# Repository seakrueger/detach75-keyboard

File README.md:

# detach75-keyboard
A 75% mechanical keyboard created for my high school PLTW capstone course. On top of being a standard mechanical keyboard, there is an integrated USB 2.0 hub with a second USB data line exposed internally. This allowed a 2.4 GHz USB receiver to be soldered on and connect to a wireless number pad for expanded functionality. 

## PCB
The design and layout of the PCB would not have been possible without this [series of articles](https://www.masterzen.fr/tag/#pcb) from Masterzen. Following his process, I adapted the matrix from a 60% layout to a 75% layout and integrated the USB 2.0 hub IC onto the USB D+/- lines. The PCB is relatively basic, being only two layers and missing several elements such as ground pours. The manufactured version of the PCB had two incorrectly placed capacitors that prevented the MCU from staying on and had to be removed; the included CAD files have been corrected. 

## Firmware
The keyboard uses the widely popular QMK firmware. QMK is the firmware of choice among keyboard enthusiasts as it is easily customizable with a rich set of features. Included is the configuration for the PCB's switch matrix as well as a basic setup of modifier keys.

To flash the PCB's MCU, first set up QMK following their guide [here](https://docs.qmk.fm/newbs_getting_started). Then, copy the contents of the Firmware directory into the QMK keyboard directory. Compile the firmware with `qmk compile -kb detach/75 -km default` and flash using QMK's [flashing guide](https://docs.qmk.fm/newbs_flashing). Use the reset push button on the underside of the PCB to initiate the ATmega bootloader; the MCU can be flashed via the USB-C port.

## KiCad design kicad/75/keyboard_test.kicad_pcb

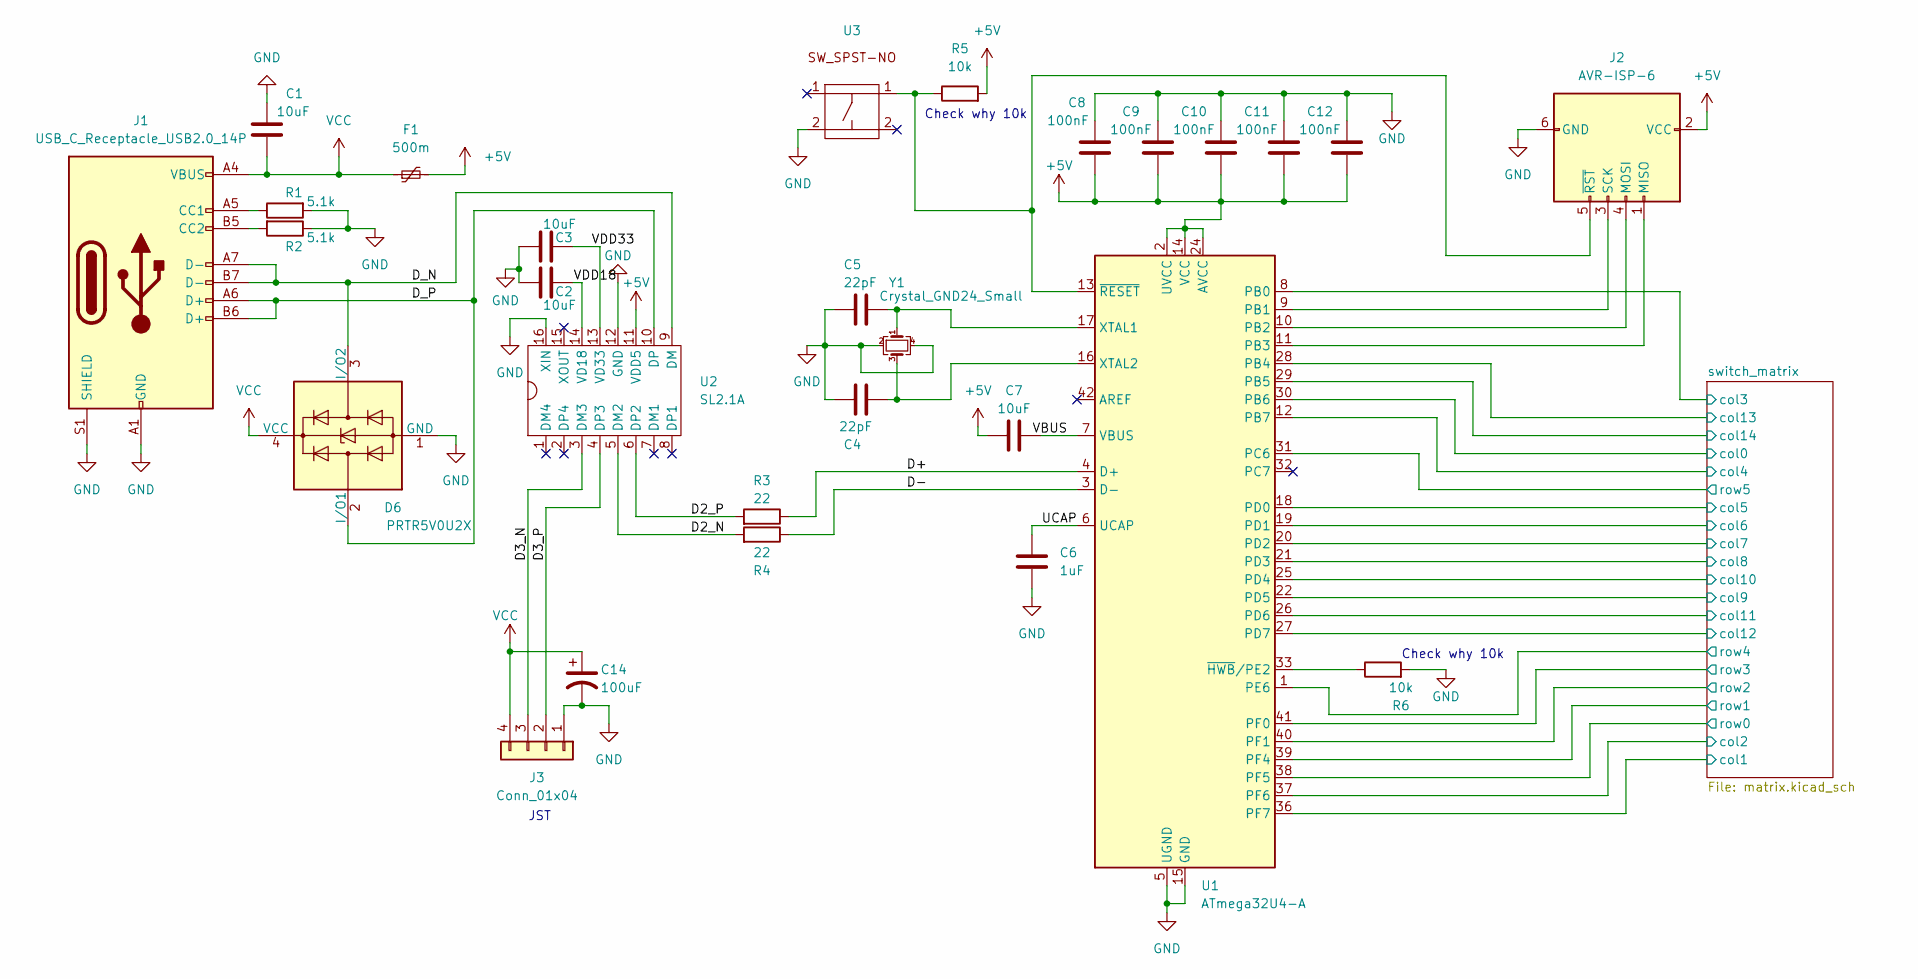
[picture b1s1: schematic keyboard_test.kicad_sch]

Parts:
C1, C2, C3, C7: 10uF; C_0805_2012Metric_Pad1.18x1.45mm_HandSolder; LCSC C95841
C4, C5: 22pF; C_0805_2012Metric_Pad1.18x1.45mm_HandSolder; LCSC C1804
C6: 1uF; C_0805_2012Metric_Pad1.18x1.45mm_HandSolder; LCSC C116352
C8, C9, C10, C11, C12: 100nF; C_0805_2012Metric_Pad1.18x1.45mm_HandSolder; LCSC C346219
C14: 100uF; C_Elec_6.3x5.4; LCSC C111600
D6: PRTR5V0U2X; SOT-143; LCSC C2827688
F1: 500m; Fuse_1206_3216Metric_Pad1.42x1.75mm_HandSolder; LCSC C70069
J1: USB_C_Receptacle_USB2.0_14P; USB_C_Receptacle_HRO_TYPE-C-31-M-12; LCSC C165948
J2: AVR-ISP-6; Reset_Pretty-Mask
J3: Conn_01x04; JST_SH_SM04B-SRSS-TB_1x04-1MP_P1.00mm_Horizontal
R1, R2: 5.1k; R_0805_2012Metric_Pad1.20x1.40mm_HandSolder; LCSC C27834
R3, R4: 22; R_0805_2012Metric_Pad1.20x1.40mm_HandSolder; LCSC C17561
R5, R6: 10k; R_0805_2012Metric_Pad1.20x1.40mm_HandSolder; LCSC C17402
U1: ATmega32U4-A; TQFP-44_10x10mm_P0.8mm; LCSC C44854
U2: SL2.1A; SO16; LCSC C6798314
U3: SW_SPST_SKQG_WithStem; LCSC C115351
Y1: Crystal_GND24_Small; Crystal_SMD_3225-4Pin_3.2x2.5mm_HandSoldering; LCSC C255909

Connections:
+5V: C7.1, C8.1, C9.1, C10.1, C11.1, C12.1, F1.2, J2.2 (VCC), R5.2, U1.2 (UVCC), U1.14 (VCC), U1.24 (AVCC), U1.34 (VCC), U1.44 (AVCC), U2.11 (VDD5)
/D2_N: R4.2, U2.5 (DM2)
/D2_P: R3.2, U2.6 (DP2)
/D3_N: J3.3, U2.3 (DM3)
/D3_P: J3.2, U2.4 (DP3)
/D+: R3.1, U1.4 (D+)
/D-: R4.1, U1.3 (D-)
/D_N: D6.3 (I/O2), J1.A7 (D-), J1.B7 (D-), U2.9 (DM)
/D_P: D6.2 (I/O1), J1.A6 (D+), J1.B6 (D+), U2.10 (DP)
/UCAP: C6.1, U1.6 (UCAP)
/VBUS: C7.2, U1.7 (VBUS)
/VDD18: C2.1, U2.14 (VD18)
/VDD33: C3.1, U2.13 (VD33)
/switch_matrix/col0: U1.30 (PB6); also elsewhere on the board
/switch_matrix/col1: U1.36 (PF7); also elsewhere on the board
/switch_matrix/col2: U1.37 (PF6); also elsewhere on the board
/switch_matrix/col3: U1.8 (PB0); also elsewhere on the board
/switch_matrix/col4: U1.12 (PB7); also elsewhere on the board
/switch_matrix/col5: U1.18 (PD0); also elsewhere on the board
/switch_matrix/col6: U1.19 (PD1); also elsewhere on the board
/switch_matrix/col7: U1.20 (PD2); also elsewhere on the board
/switch_matrix/col8: U1.21 (PD3); also elsewhere on the board
/switch_matrix/col9: U1.22 (PD5); also elsewhere on the board
/switch_matrix/col10: U1.25 (PD4); also elsewhere on the board
/switch_matrix/col11: U1.26 (PD6); also elsewhere on the board
/switch_matrix/col12: U1.27 (PD7); also elsewhere on the board
/switch_matrix/col13: U1.28 (PB4); also elsewhere on the board
/switch_matrix/col14: U1.29 (PB5); also elsewhere on the board
/switch_matrix/row0: U1.38 (PF5); also elsewhere on the board
/switch_matrix/row1: U1.39 (PF4); also elsewhere on the board
/switch_matrix/row2: U1.40 (PF1); also elsewhere on the board
/switch_matrix/row3: U1.41 (PF0); also elsewhere on the board
/switch_matrix/row4: U1.1 (PE6); also elsewhere on the board
/switch_matrix/row5: U1.31 (PC6); also elsewhere on the board
GND: C1.1, C2.2, C3.2, C4.2, C5.2, C6.2, C8.2, C9.2, C10.2, C11.2, C12.2, C14.2, D6.1 (GND), J1.A1 (GND), J1.A12 (GND), J1.B1 (GND), J1.B12 (GND), J1.S1 (SHIELD), J2.6 (GND), J3.1, R1.2, R2.1, R6.2, U1.5 (UGND), U1.15 (GND), U1.23 (GND), U1.35 (GND), U1.43 (GND), U2.12 (GND), U2.16 (XIN), U3.2, Y1.2, Y1.4
unnamed: J1.A5 (CC1), R1.1
unnamed: J1.B5 (CC2), R2.2
unnamed: J2.1 (MISO), U1.11 (PB3)
unnamed: J2.4 (MOSI), U1.10 (PB2)
unnamed: J2.3 (SCK), U1.9 (PB1)
unnamed: J2.5 (~RST), R5.1, U1.13 (~RESET), U3.1
unnamed: C5.1, U1.17 (XTAL1), Y1.1
unnamed: C4.1, U1.16 (XTAL2), Y1.3
unnamed: R6.1, U1.33 (~HWB/PE2)
VCC: C1.2, C14.1, D6.4 (VCC), F1.1, J1.A4 (VBUS), J1.A9 (VBUS), J1.B4 (VBUS), J1.B9 (VBUS), J3.4

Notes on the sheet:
Check why 10k
JST

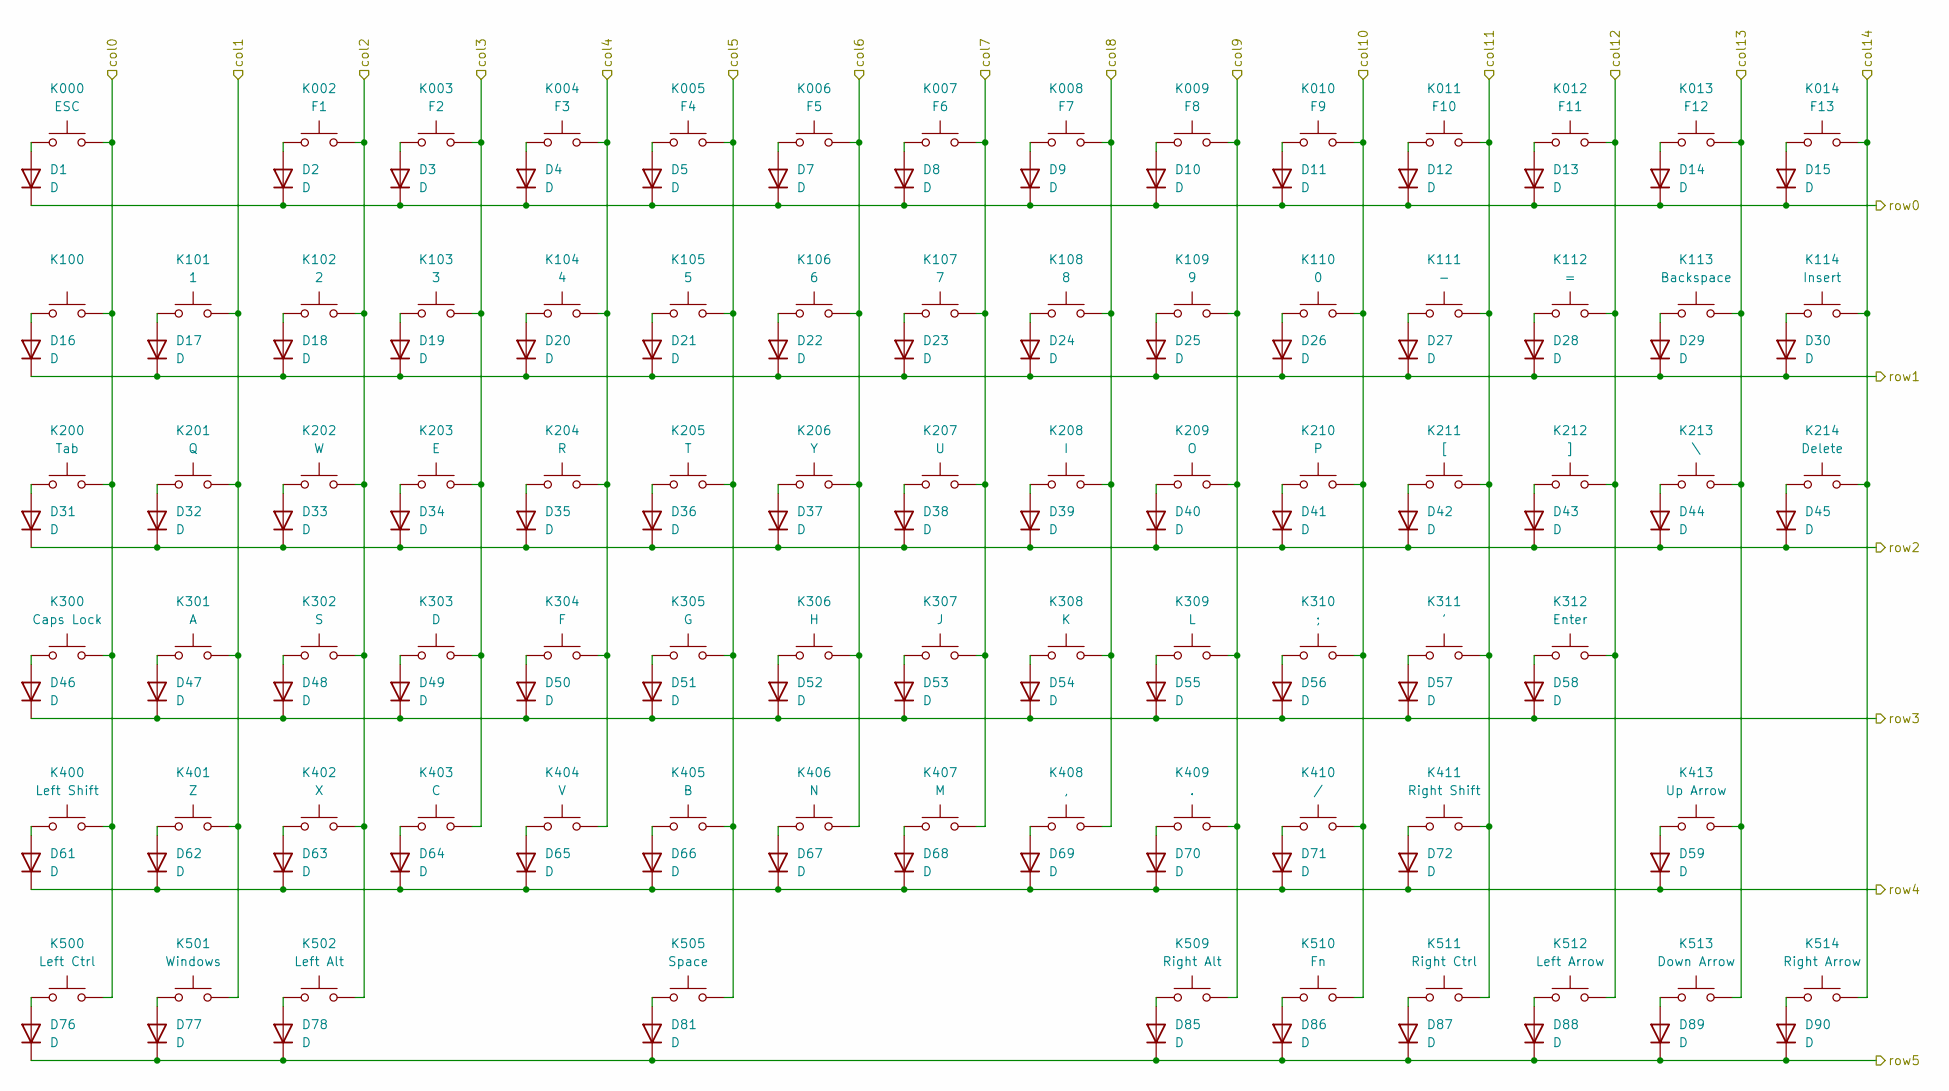
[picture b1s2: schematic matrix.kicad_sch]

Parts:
D1, D2, D3, D4, D5, D7, D8, D9, D10, D11, D12, D13, D14, D15, D16, D17, D18, D19, D20, D21, D22, D23, D24, D25, D26, D27, D28, D29, D30, D31, D32, D33, D34, D35, D36, D37, D38, D39, D40, D41, D42, D43, D44, D45, D46, D47, D48, D49, D50, D51, D52, D53, D54, D55, D56, D57, D58, D59, D61, D62, D63, D64, D65, D66, D67, D68, D69, D70, D71, D72, D76, D77, D78, D81, D85, D86, D87, D88, D89, D90: D; D_SOD-123; LCSC C77978
K000: ESC; SW_Hotswap_Kailh_MX_1.00u
K002: F1; SW_Hotswap_Kailh_MX_1.00u
K003: F2; SW_Hotswap_Kailh_MX_1.00u
K004: F3; SW_Hotswap_Kailh_MX_1.00u
K005: F4; SW_Hotswap_Kailh_MX_1.00u
K006: F5; SW_Hotswap_Kailh_MX_1.00u
K007: F6; SW_Hotswap_Kailh_MX_1.00u
K008: F7; SW_Hotswap_Kailh_MX_1.00u
K009: F8; SW_Hotswap_Kailh_MX_1.00u
K010: F9; SW_Hotswap_Kailh_MX_1.00u
K011: F10; SW_Hotswap_Kailh_MX_1.00u
K012: F11; SW_Hotswap_Kailh_MX_1.00u
K013: F12; SW_Hotswap_Kailh_MX_1.00u
K014: F13; SW_Hotswap_Kailh_MX_1.00u
K100: SW_Hotswap_Kailh_MX_1.00u
K101: 1; SW_Hotswap_Kailh_MX_1.00u
K102: 2; SW_Hotswap_Kailh_MX_1.00u
K103: 3; SW_Hotswap_Kailh_MX_1.00u
K104: 4; SW_Hotswap_Kailh_MX_1.00u
K105: 5; SW_Hotswap_Kailh_MX_1.00u
K106: 6; SW_Hotswap_Kailh_MX_1.00u
K107: 7; SW_Hotswap_Kailh_MX_1.00u
K108: 8; SW_Hotswap_Kailh_MX_1.00u
K109: 9; SW_Hotswap_Kailh_MX_1.00u
K110: 0; SW_Hotswap_Kailh_MX_1.00u
K111: -; SW_Hotswap_Kailh_MX_1.00u
K112: =; SW_Hotswap_Kailh_MX_1.00u
K113: Backspace; SW_Hotswap_Kailh_MX_2.00u
K114: Insert; SW_Hotswap_Kailh_MX_1.00u
K200: Tab; SW_Hotswap_Kailh_MX_1.50u
K201: Q; SW_Hotswap_Kailh_MX_1.00u
K202: W; SW_Hotswap_Kailh_MX_1.00u
K203: E; SW_Hotswap_Kailh_MX_1.00u
K204: R; SW_Hotswap_Kailh_MX_1.00u
K205: T; SW_Hotswap_Kailh_MX_1.00u
K206: Y; SW_Hotswap_Kailh_MX_1.00u
K207: U; SW_Hotswap_Kailh_MX_1.00u
K208: I; SW_Hotswap_Kailh_MX_1.00u
K209: O; SW_Hotswap_Kailh_MX_1.00u
K210: P; SW_Hotswap_Kailh_MX_1.00u
K211: [; SW_Hotswap_Kailh_MX_1.00u
K212: ]; SW_Hotswap_Kailh_MX_1.00u
K213: \; SW_Hotswap_Kailh_MX_1.50u
K214: Delete; SW_Hotswap_Kailh_MX_1.00u
K300: Caps Lock; SW_Hotswap_Kailh_MX_1.75u
K301: A; SW_Hotswap_Kailh_MX_1.00u
K302: S; SW_Hotswap_Kailh_MX_1.00u
K303: D; SW_Hotswap_Kailh_MX_1.00u
K304: F; SW_Hotswap_Kailh_MX_1.00u
K305: G; SW_Hotswap_Kailh_MX_1.00u
K306: H; SW_Hotswap_Kailh_MX_1.00u
K307: J; SW_Hotswap_Kailh_MX_1.00u
K308: K; SW_Hotswap_Kailh_MX_1.00u
K309: L; SW_Hotswap_Kailh_MX_1.00u
K310: ;; SW_Hotswap_Kailh_MX_1.00u
K311: '; SW_Hotswap_Kailh_MX_1.00u
K312: Enter; SW_Hotswap_Kailh_MX_2.25u
K400: Left Shift; SW_Hotswap_Kailh_MX_2.25u
K401: Z; SW_Hotswap_Kailh_MX_1.00u
K402: X; SW_Hotswap_Kailh_MX_1.00u
K403: C; SW_Hotswap_Kailh_MX_1.00u
K404: V; SW_Hotswap_Kailh_MX_1.00u
K405: B; SW_Hotswap_Kailh_MX_1.00u
K406: N; SW_Hotswap_Kailh_MX_1.00u
K407: M; SW_Hotswap_Kailh_MX_1.00u
K408: ,; SW_Hotswap_Kailh_MX_1.00u
K409: .; SW_Hotswap_Kailh_MX_1.00u
K410: /; SW_Hotswap_Kailh_MX_1.00u
K411: Right Shift; SW_Hotswap_Kailh_MX_1.75u
K413: Up Arrow; SW_Hotswap_Kailh_MX_1.00u
K500: Left Ctrl; SW_Hotswap_Kailh_MX_1.25u
K501: Windows; SW_Hotswap_Kailh_MX_1.25u
K502: Left Alt; SW_Hotswap_Kailh_MX_1.25u
K505: Space; SW_Hotswap_Kailh_MX_6.25u
K509: Right Alt; SW_Hotswap_Kailh_MX_1.00u
K510: Fn; SW_Hotswap_Kailh_MX_1.00u
K511: Right Ctrl; SW_Hotswap_Kailh_MX_1.00u
K512: Left Arrow; SW_Hotswap_Kailh_MX_1.00u
K513: Down Arrow; SW_Hotswap_Kailh_MX_1.00u
K514: Right Arrow; SW_Hotswap_Kailh_MX_1.00u

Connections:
/switch_matrix/col0: K000.2, K100.2, K200.2, K300.2, K400.2, K500.2; also elsewhere on the board
/switch_matrix/col1: K101.2, K201.2, K301.2, K401.2, K501.2; also elsewhere on the board
/switch_matrix/col2: K002.2, K102.2, K202.2, K302.2, K402.2, K502.2; also elsewhere on the board
/switch_matrix/col3: K003.2, K103.2, K203.2, K303.2, K403.2; also elsewhere on the board
/switch_matrix/col4: K004.2, K104.2, K204.2, K304.2, K404.2; also elsewhere on the board
/switch_matrix/col5: K005.2, K105.2, K205.2, K305.2, K405.2, K505.2; also elsewhere on the board
/switch_matrix/col6: K006.2, K106.2, K206.2, K306.2, K406.2; also elsewhere on the board
/switch_matrix/col7: K007.2, K107.2, K207.2, K307.2, K407.2; also elsewhere on the board
/switch_matrix/col8: K008.2, K108.2, K208.2, K308.2, K408.2; also elsewhere on the board
/switch_matrix/col9: K009.2, K109.2, K209.2, K309.2, K409.2, K509.2; also elsewhere on the board
/switch_matrix/col10: K010.2, K110.2, K210.2, K310.2, K410.2, K510.2; also elsewhere on the board
/switch_matrix/col11: K011.2, K111.2, K211.2, K311.2, K411.2, K511.2; also elsewhere on the board
/switch_matrix/col12: K012.2, K112.2, K212.2, K312.2, K512.2; also elsewhere on the board
/switch_matrix/col13: K013.2, K113.2, K213.2, K413.2, K513.2; also elsewhere on the board
/switch_matrix/col14: K014.2, K114.2, K214.2, K514.2; also elsewhere on the board
/switch_matrix/row0: D1.1 (K), D2.1 (K), D3.1 (K), D4.1 (K), D5.1 (K), D7.1 (K), D8.1 (K), D9.1 (K), D10.1 (K), D11.1 (K), D12.1 (K), D13.1 (K), D14.1 (K), D15.1 (K); also elsewhere on the board
/switch_matrix/row1: D16.1 (K), D17.1 (K), D18.1 (K), D19.1 (K), D20.1 (K), D21.1 (K), D22.1 (K), D23.1 (K), D24.1 (K), D25.1 (K), D26.1 (K), D27.1 (K), D28.1 (K), D29.1 (K), D30.1 (K); also elsewhere on the board
/switch_matrix/row2: D31.1 (K), D32.1 (K), D33.1 (K), D34.1 (K), D35.1 (K), D36.1 (K), D37.1 (K), D38.1 (K), D39.1 (K), D40.1 (K), D41.1 (K), D42.1 (K), D43.1 (K), D44.1 (K), D45.1 (K); also elsewhere on the board
/switch_matrix/row3: D46.1 (K), D47.1 (K), D48.1 (K), D49.1 (K), D50.1 (K), D51.1 (K), D52.1 (K), D53.1 (K), D54.1 (K), D55.1 (K), D56.1 (K), D57.1 (K), D58.1 (K); also elsewhere on the board
/switch_matrix/row4: D59.1 (K), D61.1 (K), D62.1 (K), D63.1 (K), D64.1 (K), D65.1 (K), D66.1 (K), D67.1 (K), D68.1 (K), D69.1 (K), D70.1 (K), D71.1 (K), D72.1 (K); also elsewhere on the board
/switch_matrix/row5: D76.1 (K), D77.1 (K), D78.1 (K), D81.1 (K), D85.1 (K), D86.1 (K), D87.1 (K), D88.1 (K), D89.1 (K), D90.1 (K); also elsewhere on the board
unnamed: D1.2 (A), K000.1
unnamed: D2.2 (A), K002.1
unnamed: D3.2 (A), K003.1
unnamed: D4.2 (A), K004.1
unnamed: D5.2 (A), K005.1
unnamed: D7.2 (A), K006.1
unnamed: D8.2 (A), K007.1
unnamed: D9.2 (A), K008.1
unnamed: D10.2 (A), K009.1
unnamed: D11.2 (A), K010.1
unnamed: D12.2 (A), K011.1
unnamed: D13.2 (A), K012.1
unnamed: D14.2 (A), K013.1
unnamed: D15.2 (A), K014.1
unnamed: D16.2 (A), K100.1
unnamed: D17.2 (A), K101.1
unnamed: D18.2 (A), K102.1
unnamed: D19.2 (A), K103.1
unnamed: D20.2 (A), K104.1
unnamed: D21.2 (A), K105.1
unnamed: D22.2 (A), K106.1
unnamed: D23.2 (A), K107.1
unnamed: D24.2 (A), K108.1
unnamed: D25.2 (A), K109.1
unnamed: D26.2 (A), K110.1
unnamed: D27.2 (A), K111.1
unnamed: D28.2 (A), K112.1
unnamed: D29.2 (A), K113.1
unnamed: D30.2 (A), K114.1
unnamed: D31.2 (A), K200.1
unnamed: D32.2 (A), K201.1
unnamed: D33.2 (A), K202.1
unnamed: D34.2 (A), K203.1
unnamed: D35.2 (A), K204.1
unnamed: D36.2 (A), K205.1
unnamed: D37.2 (A), K206.1
unnamed: D38.2 (A), K207.1
unnamed: D39.2 (A), K208.1
unnamed: D40.2 (A), K209.1
unnamed: D41.2 (A), K210.1
unnamed: D42.2 (A), K211.1
unnamed: D43.2 (A), K212.1
unnamed: D44.2 (A), K213.1
unnamed: D45.2 (A), K214.1
unnamed: D46.2 (A), K300.1
unnamed: D47.2 (A), K301.1
unnamed: D48.2 (A), K302.1
unnamed: D49.2 (A), K303.1
unnamed: D50.2 (A), K304.1
unnamed: D51.2 (A), K305.1
unnamed: D52.2 (A), K306.1
unnamed: D53.2 (A), K307.1
unnamed: D54.2 (A), K308.1
unnamed: D55.2 (A), K309.1
unnamed: D56.2 (A), K310.1
unnamed: D57.2 (A), K311.1
unnamed: D58.2 (A), K312.1
unnamed: D59.2 (A), K413.1
unnamed: D61.2 (A), K400.1
unnamed: D62.2 (A), K401.1
unnamed: D63.2 (A), K402.1
unnamed: D64.2 (A), K403.1
unnamed: D65.2 (A), K404.1
unnamed: D66.2 (A), K405.1
unnamed: D67.2 (A), K406.1
unnamed: D68.2 (A), K407.1
unnamed: D69.2 (A), K408.1
unnamed: D70.2 (A), K409.1
unnamed: D71.2 (A), K410.1
unnamed: D72.2 (A), K411.1
unnamed: D76.2 (A), K500.1
unnamed: D77.2 (A), K501.1
unnamed: D78.2 (A), K502.1
unnamed: D81.2 (A), K505.1
unnamed: D85.2 (A), K509.1
unnamed: D86.2 (A), K510.1
unnamed: D87.2 (A), K511.1
unnamed: D88.2 (A), K512.1
unnamed: D89.2 (A), K513.1
unnamed: D90.2 (A), K514.1

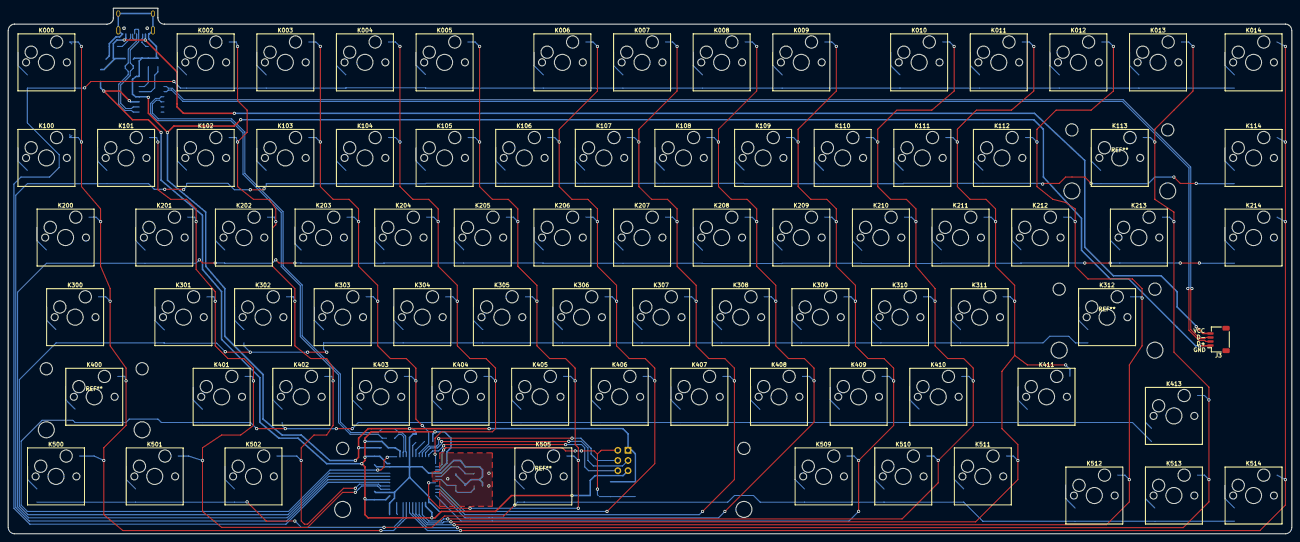
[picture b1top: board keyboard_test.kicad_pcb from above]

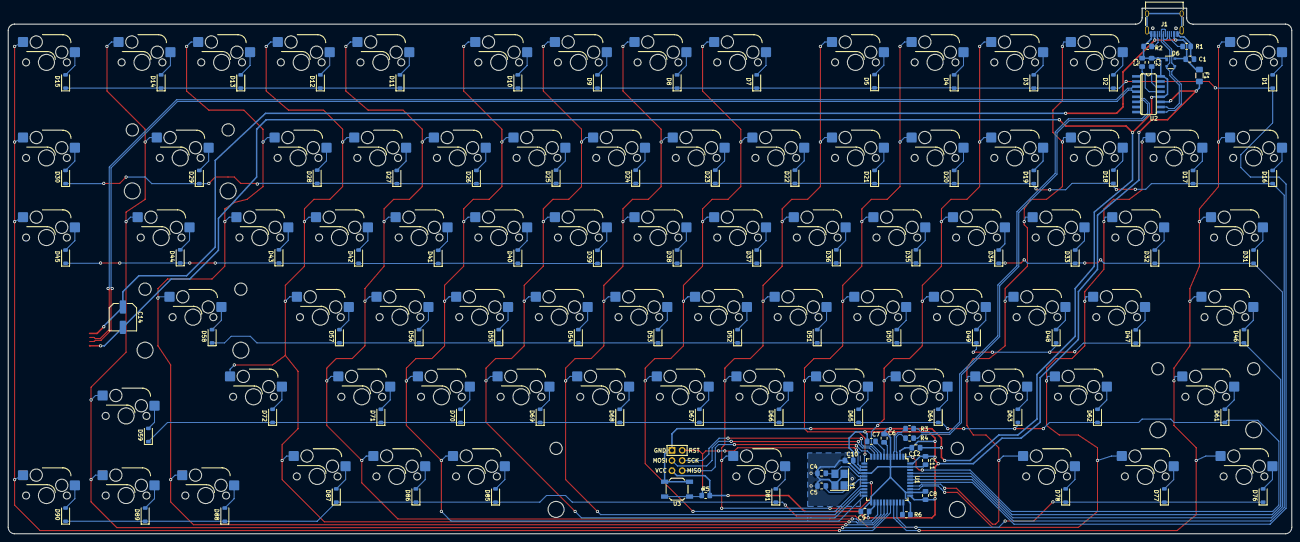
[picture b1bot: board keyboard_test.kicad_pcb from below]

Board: 2 copper layers, 319.9 x 131.0 mm, 188 parts (107 on the bottom side), 125 nets.

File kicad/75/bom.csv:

Comment,Designator,Footprint,LCSC
10uF,"C1,C2,C3,C7",C_0805_2012Metric_Pad1.18x1.45mm_HandSolder,C95841
100uF,C14,C_Elec_6.3x5.4,C111600
22pF,"C4,C5",C_0805_2012Metric_Pad1.18x1.45mm_HandSolder,C1804
1uF,C6,C_0805_2012Metric_Pad1.18x1.45mm_HandSolder,C116352
100nF,"C8,C9,C10,C11,C12",C_0805_2012Metric_Pad1.18x1.45mm_HandSolder,C346219
D,"D1,D2,D3,D4,D5,D7,D8,D9,D10,D11,D12,D13,D14,D15,D16,D17,D18,D19,D20,D21,D22,D23,D24,D25,D26,D27,D28,D29,D30,D31,D32,D33,D34,D35,D36,D37,D38,D39,D40,D41,D42,D43,D44,D45,D46,D47,D48,D49,D50,D51,D52,D53,D54,D55,D56,D57,D58,D59,D61,D62,D63,D64,D65,D66,D67,D68,D69,D70,D71,D72,D76,D77,D78,D81,D85,D86,D87,D88,D89,D90",D_SOD-123,C77978
PRTR5V0U2X,D6,SOT-143,C2827688
500m,F1,Fuse_1206_3216Metric_Pad1.42x1.75mm_HandSolder,C70069
USB_C_Receptacle_USB2.0_14P,J1,USB_C_Receptacle_HRO_TYPE-C-31-M-12,C165948
AVR-ISP-6,J2,random-keyboard-parts:Reset_Pretty-Mask,
Conn_01x04,J3,Connector_JST:JST_SH_SM04B-SRSS-TB_1x04-1MP_P1.00mm_Horizontal,
ESC,K000,PCM_Switch_Keyboard_Hotswap_Kailh:SW_Hotswap_Kailh_MX_1.00u,
F1,K002,PCM_Switch_Keyboard_Hotswap_Kailh:SW_Hotswap_Kailh_MX_1.00u,
F2,K003,PCM_Switch_Keyboard_Hotswap_Kailh:SW_Hotswap_Kailh_MX_1.00u,
F3,K004,PCM_Switch_Keyboard_Hotswap_Kailh:SW_Hotswap_Kailh_MX_1.00u,
F4,K005,PCM_Switch_Keyboard_Hotswap_Kailh:SW_Hotswap_Kailh_MX_1.00u,
F5,K006,PCM_Switch_Keyboard_Hotswap_Kailh:SW_Hotswap_Kailh_MX_1.00u,
F6,K007,PCM_Switch_Keyboard_Hotswap_Kailh:SW_Hotswap_Kailh_MX_1.00u,
F7,K008,PCM_Switch_Keyboard_Hotswap_Kailh:SW_Hotswap_Kailh_MX_1.00u,
F8,K009,PCM_Switch_Keyboard_Hotswap_Kailh:SW_Hotswap_Kailh_MX_1.00u,
F9,K010,PCM_Switch_Keyboard_Hotswap_Kailh:SW_Hotswap_Kailh_MX_1.00u,
F10,K011,PCM_Switch_Keyboard_Hotswap_Kailh:SW_Hotswap_Kailh_MX_1.00u,
F11,K012,PCM_Switch_Keyboard_Hotswap_Kailh:SW_Hotswap_Kailh_MX_1.00u,
F12,K013,PCM_Switch_Keyboard_Hotswap_Kailh:SW_Hotswap_Kailh_MX_1.00u,
F13,K014,PCM_Switch_Keyboard_Hotswap_Kailh:SW_Hotswap_Kailh_MX_1.00u,
~,K100,PCM_Switch_Keyboard_Hotswap_Kailh:SW_Hotswap_Kailh_MX_1.00u,
1,K101,PCM_Switch_Keyboard_Hotswap_Kailh:SW_Hotswap_Kailh_MX_1.00u,
2,K102,PCM_Switch_Keyboard_Hotswap_Kailh:SW_Hotswap_Kailh_MX_1.00u,
3,K103,PCM_Switch_Keyboard_Hotswap_Kailh:SW_Hotswap_Kailh_MX_1.00u,
4,K104,PCM_Switch_Keyboard_Hotswap_Kailh:SW_Hotswap_Kailh_MX_1.00u,
5,K105,PCM_Switch_Keyboard_Hotswap_Kailh:SW_Hotswap_Kailh_MX_1.00u,
6,K106,PCM_Switch_Keyboard_Hotswap_Kailh:SW_Hotswap_Kailh_MX_1.00u,
7,K107,PCM_Switch_Keyboard_Hotswap_Kailh:SW_Hotswap_Kailh_MX_1.00u,
8,K108,PCM_Switch_Keyboard_Hotswap_Kailh:SW_Hotswap_Kailh_MX_1.00u,
9,K109,PCM_Switch_Keyboard_Hotswap_Kailh:SW_Hotswap_Kailh_MX_1.00u,
0,K110,PCM_Switch_Keyboard_Hotswap_Kailh:SW_Hotswap_Kailh_MX_1.00u,
-,K111,PCM_Switch_Keyboard_Hotswap_Kailh:SW_Hotswap_Kailh_MX_1.00u,
=,K112,PCM_Switch_Keyboard_Hotswap_Kailh:SW_Hotswap_Kailh_MX_1.00u,
Backspace,K113,PCM_Switch_Keyboard_Hotswap_Kailh:SW_Hotswap_Kailh_MX_2.00u,
Insert,K114,PCM_Switch_Keyboard_Hotswap_Kailh:SW_Hotswap_Kailh_MX_1.00u,
Tab,K200,PCM_Switch_Keyboard_Hotswap_Kailh:SW_Hotswap_Kailh_MX_1.50u,
Q,K201,PCM_Switch_Keyboard_Hotswap_Kailh:SW_Hotswap_Kailh_MX_1.00u,
W,K202,PCM_Switch_Keyboard_Hotswap_Kailh:SW_Hotswap_Kailh_MX_1.00u,
E,K203,PCM_Switch_Keyboard_Hotswap_Kailh:SW_Hotswap_Kailh_MX_1.00u,
R,K204,PCM_Switch_Keyboard_Hotswap_Kailh:SW_Hotswap_Kailh_MX_1.00u,
T,K205,PCM_Switch_Keyboard_Hotswap_Kailh:SW_Hotswap_Kailh_MX_1.00u,
Y,K206,PCM_Switch_Keyboard_Hotswap_Kailh:SW_Hotswap_Kailh_MX_1.00u,
U,K207,PCM_Switch_Keyboard_Hotswap_Kailh:SW_Hotswap_Kailh_MX_1.00u,
I,K208,PCM_Switch_Keyboard_Hotswap_Kailh:SW_Hotswap_Kailh_MX_1.00u,
O,K209,PCM_Switch_Keyboard_Hotswap_Kailh:SW_Hotswap_Kailh_MX_1.00u,
P,K210,PCM_Switch_Keyboard_Hotswap_Kailh:SW_Hotswap_Kailh_MX_1.00u,
[,K211,PCM_Switch_Keyboard_Hotswap_Kailh:SW_Hotswap_Kailh_MX_1.00u,
],K212,PCM_Switch_Keyboard_Hotswap_Kailh:SW_Hotswap_Kailh_MX_1.00u,
\,K213,PCM_Switch_Keyboard_Hotswap_Kailh:SW_Hotswap_Kailh_MX_1.50u,
Delete,K214,PCM_Switch_Keyboard_Hotswap_Kailh:SW_Hotswap_Kailh_MX_1.00u,
Caps Lock,K300,PCM_Switch_Keyboard_Hotswap_Kailh:SW_Hotswap_Kailh_MX_1.75u,
A,K301,PCM_Switch_Keyboard_Hotswap_Kailh:SW_Hotswap_Kailh_MX_1.00u,
S,K302,PCM_Switch_Keyboard_Hotswap_Kailh:SW_Hotswap_Kailh_MX_1.00u,
D,K303,PCM_Switch_Keyboard_Hotswap_Kailh:SW_Hotswap_Kailh_MX_1.00u,
F,K304,PCM_Switch_Keyboard_Hotswap_Kailh:SW_Hotswap_Kailh_MX_1.00u,
G,K305,PCM_Switch_Keyboard_Hotswap_Kailh:SW_Hotswap_Kailh_MX_1.00u,
H,K306,PCM_Switch_Keyboard_Hotswap_Kailh:SW_Hotswap_Kailh_MX_1.00u,
J,K307,PCM_Switch_Keyboard_Hotswap_Kailh:SW_Hotswap_Kailh_MX_1.00u,
K,K308,PCM_Switch_Keyboard_Hotswap_Kailh:SW_Hotswap_Kailh_MX_1.00u,
L,K309,PCM_Switch_Keyboard_Hotswap_Kailh:SW_Hotswap_Kailh_MX_1.00u,
;,K310,PCM_Switch_Keyboard_Hotswap_Kailh:SW_Hotswap_Kailh_MX_1.00u,
',K311,PCM_Switch_Keyboard_Hotswap_Kailh:SW_Hotswap_Kailh_MX_1.00u,
Enter,K312,PCM_Switch_Keyboard_Hotswap_Kailh:SW_Hotswap_Kailh_MX_2.25u,
Left Shift,K400,PCM_Switch_Keyboard_Hotswap_Kailh:SW_Hotswap_Kailh_MX_2.25u,
Z,K401,PCM_Switch_Keyboard_Hotswap_Kailh:SW_Hotswap_Kailh_MX_1.00u,
X,K402,PCM_Switch_Keyboard_Hotswap_Kailh:SW_Hotswap_Kailh_MX_1.00u,
C,K403,PCM_Switch_Keyboard_Hotswap_Kailh:SW_Hotswap_Kailh_MX_1.00u,
V,K404,PCM_Switch_Keyboard_Hotswap_Kailh:SW_Hotswap_Kailh_MX_1.00u,
B,K405,PCM_Switch_Keyboard_Hotswap_Kailh:SW_Hotswap_Kailh_MX_1.00u,
N,K406,PCM_Switch_Keyboard_Hotswap_Kailh:SW_Hotswap_Kailh_MX_1.00u,
M,K407,PCM_Switch_Keyboard_Hotswap_Kailh:SW_Hotswap_Kailh_MX_1.00u,
",",K408,PCM_Switch_Keyboard_Hotswap_Kailh:SW_Hotswap_Kailh_MX_1.00u,
.,K409,PCM_Switch_Keyboard_Hotswap_Kailh:SW_Hotswap_Kailh_MX_1.00u,
/,K410,PCM_Switch_Keyboard_Hotswap_Kailh:SW_Hotswap_Kailh_MX_1.00u,
Right Shift,K411,PCM_Switch_Keyboard_Hotswap_Kailh:SW_Hotswap_Kailh_MX_1.75u,
Up Arrow,K413,PCM_Switch_Keyboard_Hotswap_Kailh:SW_Hotswap_Kailh_MX_1.00u,
Left Ctrl,K500,PCM_Switch_Keyboard_Hotswap_Kailh:SW_Hotswap_Kailh_MX_1.25u,
Windows,K501,PCM_Switch_Keyboard_Hotswap_Kailh:SW_Hotswap_Kailh_MX_1.25u,
Left Alt,K502,PCM_Switch_Keyboard_Hotswap_Kailh:SW_Hotswap_Kailh_MX_1.25u,
Space,K505,PCM_Switch_Keyboard_Hotswap_Kailh:SW_Hotswap_Kailh_MX_6.25u,
Right Alt,K509,PCM_Switch_Keyboard_Hotswap_Kailh:SW_Hotswap_Kailh_MX_1.00u,
Fn,K510,PCM_Switch_Keyboard_Hotswap_Kailh:SW_Hotswap_Kailh_MX_1.00u,
Right Ctrl,K511,PCM_Switch_Keyboard_Hotswap_Kailh:SW_Hotswap_Kailh_MX_1.00u,
Left Arrow,K512,PCM_Switch_Keyboard_Hotswap_Kailh:SW_Hotswap_Kailh_MX_1.00u,
Down Arrow,K513,PCM_Switch_Keyboard_Hotswap_Kailh:SW_Hotswap_Kailh_MX_1.00u,
Right Arrow,K514,PCM_Switch_Keyboard_Hotswap_Kailh:SW_Hotswap_Kailh_MX_1.00u,
5.1k,"R1,R2",R_0805_2012Metric_Pad1.20x1.40mm_HandSolder,C27834
22,"R3,R4",R_0805_2012Metric_Pad1.20x1.40mm_HandSolder,C17561
10k,"R5,R6",R_0805_2012Metric_Pad1.20x1.40mm_HandSolder,C17402
ATmega32U4-A,U1,TQFP-44_10x10mm_P0.8mm,C44854
SL2.1A,U2,SO16,C6798314
~,U3,SW_SPST_SKQG_WithStem,C115351
Crystal_GND24_Small,Y1,Crystal_SMD_3225-4Pin_3.2x2.5mm_HandSoldering,C255909

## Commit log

2024-06-04 Add initial firmware
2024-06-04 Final keyboard design
2025-05-08 Added descriptive README.md of project
